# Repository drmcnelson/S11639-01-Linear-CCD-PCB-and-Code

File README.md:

# S11639-01-Linear-CCD-PCB-and-Code

By Dr M. C. Nelson, Copyright 2020-2025

Original repository [github.com/drmcnelson/S11639-01-Linear-CCD-PCB-and-Code](https://github.com/drmcnelson/S11639-01-Linear-CCD-PCB-and-Code)

This repo provides electronics, firmware and host software for the Hamamatsu S11639-01, a linear CCD sensor that has high sensitivity at 1300V/lx s and low dark noise at 0.2mV (for a 10msec exposure).  With saturation at 2V, the dynamic range is 10,000.
The electrical design is implemented as a two board set, sensor and controller, for mechanical stability and interchangeability.
The sensor board has the socketed sensor, logic gates to drive the pins, and a low noise all differential analog section with a high precision differential 16 bit ADC.
The controller operates the sensor and interacts with a host computer over USB, and has pins for trigger, gate, sync and busy signals.
The command interface is human readable ascii, data transfers are selectable in ascii or binary.

N.B.  This is an update to bring the S11639-0 board into compatibility with the new connector layout for our controller boards.   This design is not yet built, sponsors are welcome.  Please click the sponsor button at the top of the page.

*The original boards and their matching controllers are in the subdirecty labeled [Rev0Boards](./Rev0Boards).*

This version of the board is designed to be used with either of the our controllers, the [Teensy 4.0 based controller](https://github.com/drmcnelson/SPI-Instrumentation-Controller-T4.0) 
and the [Teensy 4.1 based controller](https://github.com/drmcnelson/SPI-Instrumentation-Controller-T4.1).
In principle, the S11639-01 could be used with a number of different Arduino boards.  After some extensive and detailed testing, we prefer the Teensy 4.x boards.  These have good implementations for 16 bit transfers over SPI and they have 480MHz USB for fast transfers to the host computer.

The firmware, which runs in the controller, provides high end functionality including clocked, triggered, and gated operation.
In the firmware, codes that are specific to the sensor are in a separate c++ file and header.  The "sketch file" implements a command interface and calls the sensor code to do the "work" of collecting frames in various operating modes.  The codes throughout, use the standard Arduino libraries plus a small number of optional register level enhancements for the i.MX RT MCU that provide faster and more constant interrupt latency and SPI transfers with less overhead.

## Sensor board details
The following image shows the circuit side of the sensor board with the high precision low noise differential front end (dual opamp lower right, adjacent to the video out pin from the sensor) interfaced to a differential 16bit 1MSPS ADC, and logic level converters (center) for the external digital interface.
The sensor is socketed on the reverse side. 
SPI and logic signals are brought to the double row header at the top edge of the board (ribbon cable compatible).
The external logic level is set by VDD supplied by the controller card.
Power for the sensor and other circuit elements is 5V and supplied by a separate connector.
The small jumper top center near the double row header, selects whether the CNVST pin on the ADC is connected to the TRG signal from the sensor or to the host processor.
(The firmware at present assumes the CNVST pin is connected to the MCU.)
The jumper and header (lower left) selects the internal 4.096V reference or provides a connector for an external reference.
The output from the analog section is available on the three pin header center bottom.
The trim pot should be set to 1.6V for sensors meeting the "typical" spec with output from 0.6V to 2.6V, there is a test point next to the trim pot labeled Voffset where the offset voltage can be measured.

## T4.0 Controller board details
Please refer to the repo at 
The following describes the T4.0 based controller. The double row header across the top matches that on the sensor board.  The two boards should be connected by a ribbon cable that can be a few inches in length, and by a two wire cable for power, between the connectors labeled "5V" upper left on this board and upper left on the sensor board.  (The power cable will cross over the ribbon cable when the boards are positioned correctly and joined by a ribbon cable.)
The single row headers provides access to the digital interface signals and provides additional pins to the right for a trigger input, sync and busy ouputs and spare digital I/O pin.   The double row header on the left provides access to the onboard analog digital converters and any of these can be used for digitial I/O.  While all of these have diode protection, users should be cognizant that the Teensy is not 5V tolerant. 

Running the supplied sketch (see the Firmware directory), the controller appears as a serial port or com port with a human readable command interface.  There is a help command that produces a listing of all of the available commands.  The device can collect (a) single frames, (b) clocked series of frames, (c) triggered single frames, (d) triggered sets of clocked frames (i.e. triggered kinetic series), and (e) gated frames.  There are commands to set the sense (hi/low) of the trigger input and each of the digital outputs, and to set whether the sync output is asserted at the beginning of each frame or series.  There is a "hold off" that can be used to triggered an external device and then wait for a fixed time before collecting a frame.  Busy is asserted whenever the device is active and until data has been transferred to the host computer.   A Python utility and class library and a C language utility and library provide two options for working with the device and integrating into equipment and experiments 

## T4.1 Controller board details
The Teensy 4.1 controller is similar to the T4.0 version, but with more connectors.
In the following image, the long connector across the top corresponds to the 20 connector in the T4.0 controller.  This where the CCD connects. 
Filtered +5V power comes from the connector on the lower right.
The keyed connectors on the left, top and bottom are SPI interfaces 0 and 1.
Analog inputs are to the right of the SPI1 connector
Trigger, sync and busy are implemented in firmware on pins 0, 1, and 2.  These are brought out to a the double row header upper right, so that each pin has a ground pin.
The single row headers provide monitoring points and extended set of digital I/O pins.

## Example Spectrometer
The following shows a spectrometer built with the S11639-0 and a fluorescent lamp spectrum collected through an optical fiber and 200um slit and single 100ms exposure, with the fluorescent ceiling lamp at a distance of about 2 meters from the end of the fiber.  (At a 10ms exposure the background is 0.5mV as listed in the datasheet for the sensor.) The sensor board is mounted in a frame that allows adjustment to position the sensor on the focus.  The control board is mounted outside on the light tight cover, for easy access to the pins without disturibing the sensor board, and connected to the sensor board via a 5 inch long ribbon cable and power (twisted red and black wires). Notice that all of the optical mounts are 3-d printed.  The base plate was purchased on Amazon, the sma905 port, slit and lenses on ebay and the transmission grating from Thorlabs.

## Availability and Sponsorhip
This repo and its contents are provided without warranty or representation of suitability for any purpose whatsoever.

Feel free to build this for your own use or in your lab.  The intent is to support access to doing good science for those who are not as well funded as others.  Commercial use is subject to review and approval, per this criterion.

If you would like a preassembled board, please consider sponsoring and please contact me so that I can get a current cost of materials.

Sponsorship is very much appreciated.  Please click the sponsor button and help us make this and more devices available and support our effort to make doing science more accessible.

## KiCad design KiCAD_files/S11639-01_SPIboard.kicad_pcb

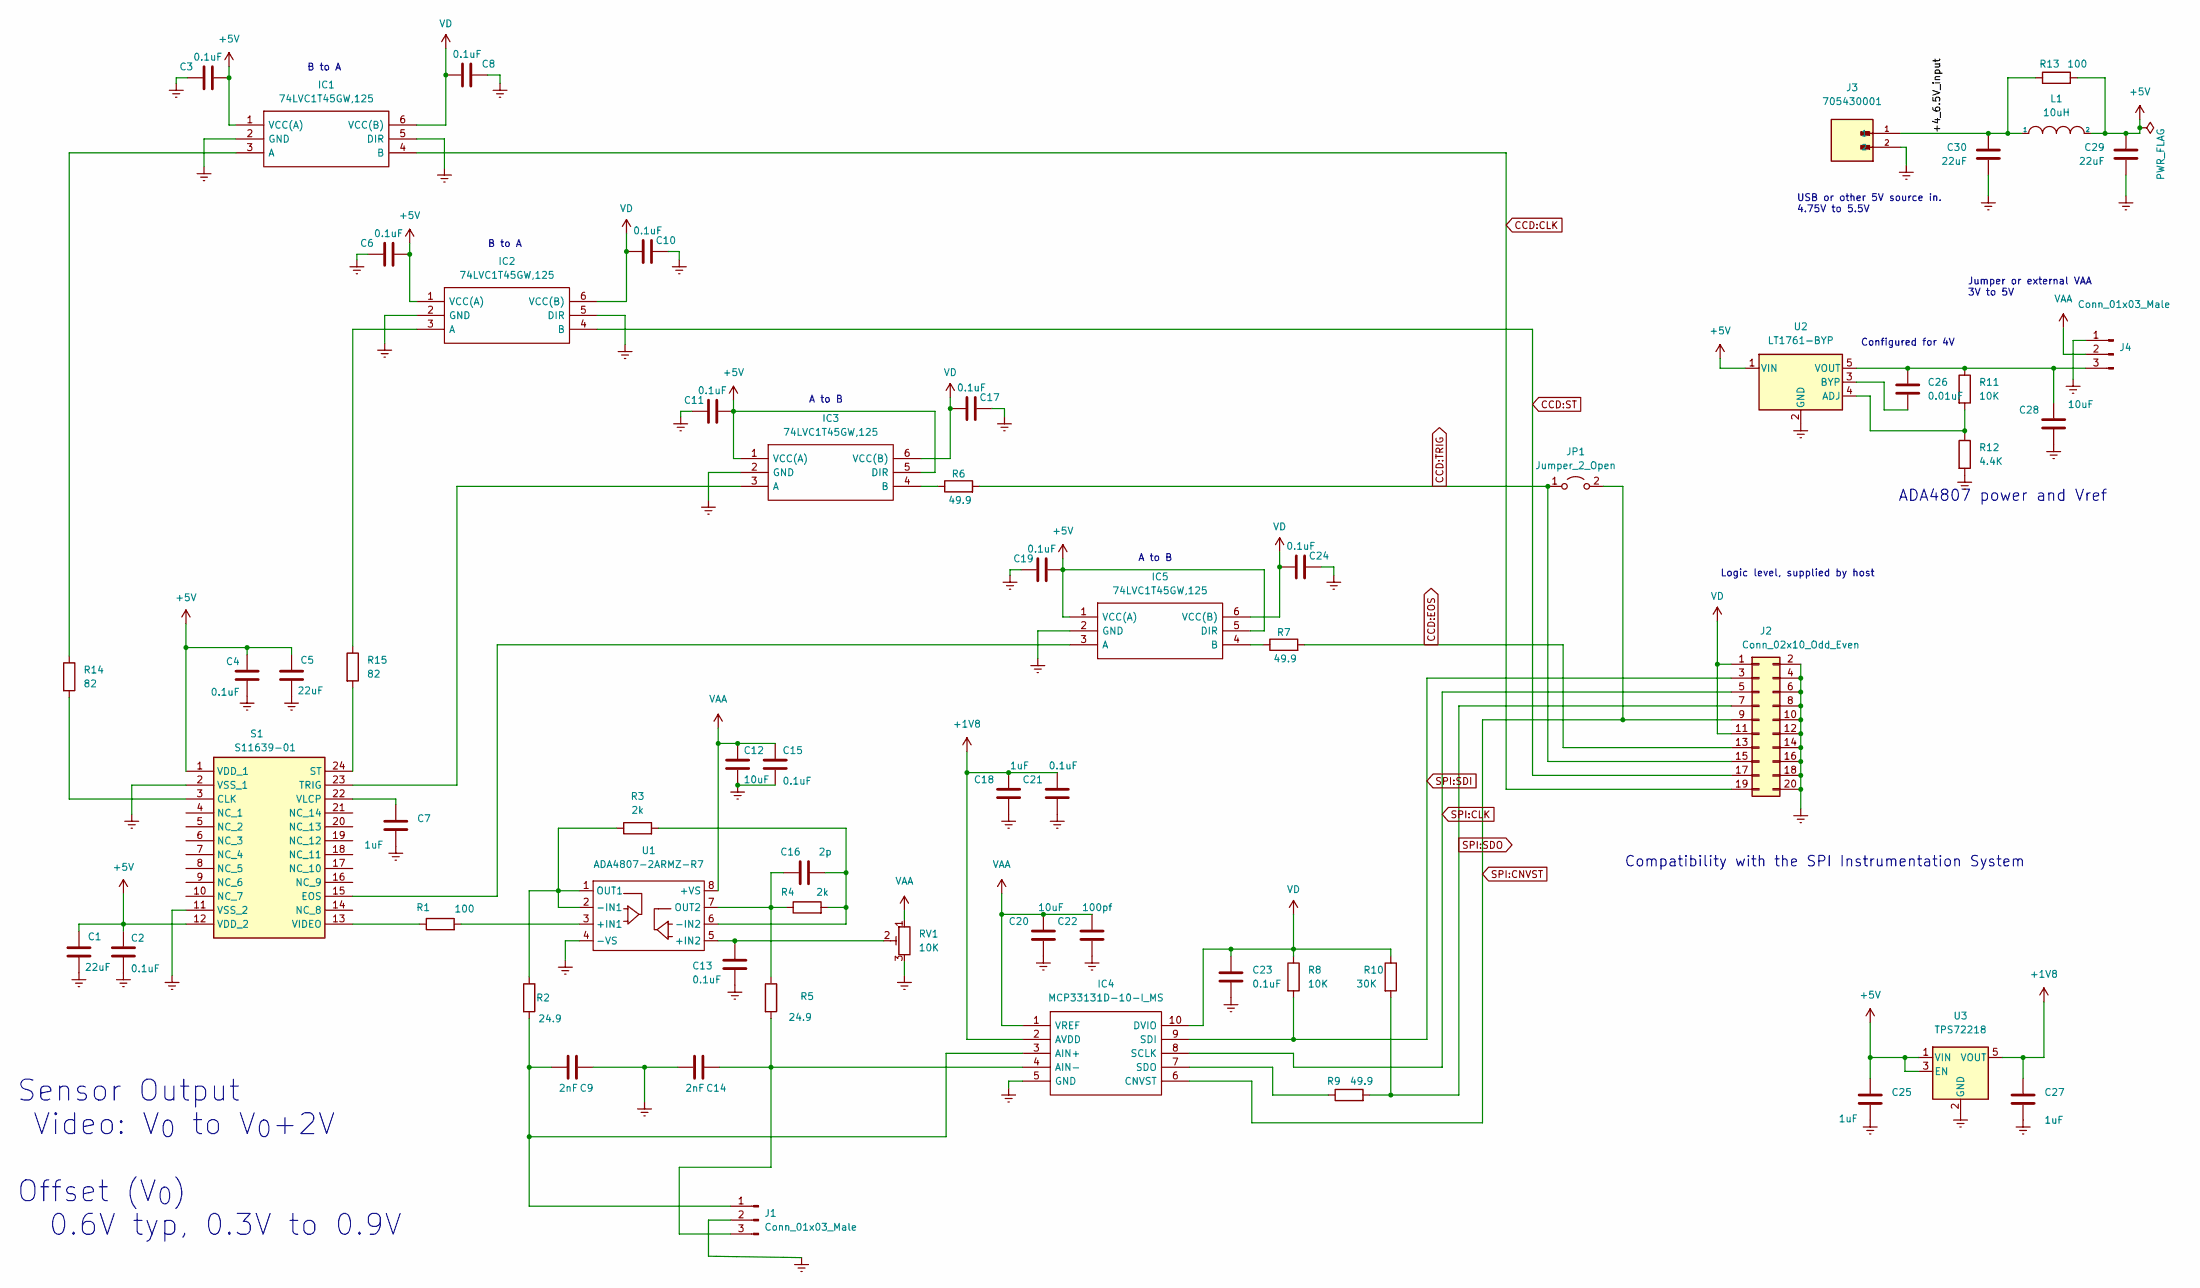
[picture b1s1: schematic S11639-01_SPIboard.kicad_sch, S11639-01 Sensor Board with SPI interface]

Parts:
C1, C5, C29, C30: 22uF; C_0805_2012Metric; Digikey 311-1903-1-ND
C2, C3, C4, C6, C8, C10, C11, C13, C15, C17, C19, C21, C23, C24: 0.1uF; C_0603_1608Metric; Digikey 445-5666-1-ND
C7, C18, C25, C27: 1uF; C_0603_1608Metric; Digikey 490-10673-1-ND
C9, C14: 2nF; C_0603_1608Metric; Digikey 311-1743-1-ND
C12, C20, C28: 10uF; C_0603_1608Metric; Digikey 490-18214-1-ND
C16: 2p; C_0603_1608Metric; Digikey 311-3827-1-ND
C22: 100pf; C_0603_1608Metric; Digikey 399-17391-1-ND
C26: 0.01uF; C_0402_1005Metric; Digikey 311-1337-1-ND
IC1, IC2, IC3, IC5: 74LVC1T45GW,125; SOT65P210X110-6N; Manufacturer_Part_Number 74LVC1T45GW,125; Digikey 1727-4560-1-ND
IC4: MCP33131D-10-I_MS; MSOP-10_3x3mm_P0.5mm; Manufacturer_Part_Number MCP33131D-10-I/MS; Mouser Part Number 579-MCP33131D10IMS
J1, J4: Conn_01x03_Male; PinHeader_1x03_P2.54mm_Vertical; Digikey 3M156268-03-ND
J2: Conn_02x10_Odd_Even; PinHeader_2x10_P2.54mm_Vertical; Digikey 3M156308-20-ND
J3: 705430001; MOLEX_705430001; PARTREV M1; Digikey WM4800-ND
JP1: Jumper_2_Open; PinHeader_1x02_P1.27mm_Vertical; Digikey S9014E-02-ND
L1: 10uH; L_Taiyo-Yuden_NR-40xx; Digikey 587-2886-1-ND
R1, R13: 100; R_0603_1608Metric; Digikey RNCP0603FTD100RCT-ND
R2, R5: 24.9; R_0603_1608Metric; Digikey 2019-RK73H1JTTD24R9FCT-ND
R3, R4: 2k; R_0603_1608Metric; Digikey P2.0KDBCT-ND
R6, R7, R9: 49.9; R_0603_1608Metric; Digikey RMCF0603FT49R9CT-ND
R8: 10K; R_0603_1608Metric; Digikey 311-10.0KHRCT-ND
R10: 30K; R_0603_1608Metric; Digikey 311-30.0KHRCT-ND
R11: 10K; R_0402_1005Metric; Digikey A127415CT-ND
R12: 4.4K; R_0402_1005Metric; Digikey YAG4274CT-ND
R14, R15: 82; R_0603_1608Metric; Digikey 311-82.0HRCT-ND
RV1: 10K; TRIM_3296W-1-502LF; Digikey 3296W-103LF-ND
S1: S11639-01; DIP-24_W10.16mm_Socket; Manufacturer_Part_Number S11639-01
U1: ADA4807-2ARMZ-R7; MSOP-8_3x3mm_P0.65mm; Digikey ADA4807-2ARMZ-R7CT-ND
U2: LT1761-BYP; TSOT-23-5; Digikey 505-LT1761ES5-BYP#TRMPBFCT-ND
U3: TPS72218; SOT-23-5; Digikey 296-12523-1-ND

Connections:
+1V8: C18.1, C21.1, C27.1, IC4.2 (AVDD), U3.5 (VOUT)
+5V: C1.1, C2.1, C3.1, C4.1, C5.1, C6.1, C11.1, C19.1, C25.1, C29.1, IC1.1 (VCC(A)), IC2.1 (VCC(A)), IC3.1 (VCC(A)), IC3.5 (DIR), IC5.1 (VCC(A)), IC5.5 (DIR), L1.2, R13.2, S1.1 (VDD_1), S1.12 (VDD_2), U2.1 (VIN), U3.1 (VIN), U3.3 (EN)
/+4_6.5V_input: C30.1, J3.1, L1.1, R13.1
CCD:CLK: IC1.4 (B), J2.19
CCD:EOS: J2.13, R7.2
CCD:ST: IC2.4 (B), J2.17
CCD:TRIG: J2.15, JP1.1 (A), R6.2
Earth: C1.2, C2.2, C3.2, C4.2, C5.2, C6.2, C7.2, C8.2, C9.1, C10.2, C11.2, C12.2, C13.2, C14.2, C15.2, C17.2, C18.2, C19.2, C20.2, C21.2, C22.2, C23.2, C24.2, C25.2, C27.2, C28.2, C29.2, C30.2, IC1.2 (GND), IC1.5 (DIR), IC2.2 (GND), IC2.5 (DIR), IC3.2 (GND), IC4.5 (GND), IC5.2 (GND), J1.2, J2.2, J2.4, J2.6, J2.8, J2.10, J2.12, J2.14, J2.16, J2.18, J2.20, J3.2, J4.1, R12.2, RV1.3, S1.2 (VSS_1), S1.11 (VSS_2), U1.4 (-VS), U2.2 (GND), U3.2 (GND)
unnamed: IC1.3 (A), R14.1
unnamed: IC2.3 (A), R15.1
unnamed: IC3.3 (A), S1.23 (TRIG)
unnamed: IC3.4 (B), R6.1
unnamed: C9.2, IC4.3 (AIN+), J1.1, R2.2
unnamed: C14.1, IC4.4 (AIN-), J1.3, R5.2
unnamed: IC4.7 (SDO), R9.1
unnamed: IC5.3 (A), S1.15 (EOS)
unnamed: IC5.4 (B), R7.1
unnamed: C26.1, C28.1, J4.3, R11.1, U2.5 (VOUT)
unnamed: R14.2, S1.3 (CLK)
unnamed: R15.2, S1.24 (ST)
unnamed: R1.1, S1.13 (VIDEO)
unnamed: C7.1, S1.22 (VLCP)
unnamed: R1.2, U1.3 (+IN1)
unnamed: C13.1, RV1.2, U1.5 (+IN2)
unnamed: R2.1, R3.1, U1.1 (OUT1), U1.2 (-IN1)
unnamed: C16.2, R3.2, R4.2, U1.6 (-IN2)
unnamed: C16.1, R4.1, R5.1, U1.7 (OUT2)
unnamed: R11.2, R12.1, U2.4 (ADJ)
unnamed: C26.2, U2.3 (BYP)
SPI:CLK: IC4.8 (SCLK), J2.5
SPI:CNVST: IC4.6 (CNVST), J2.9, JP1.2 (B)
SPI:SDI: IC4.9 (SDI), J2.3, R8.2
SPI:SDO: J2.7, R9.2, R10.2
VAA: C12.1, C15.1, C20.1, C22.1, IC4.1 (VREF), J4.2, RV1.1, U1.8 (+VS)
VD: C8.1, C10.1, C17.1, C23.1, C24.1, IC1.6 (VCC(B)), IC2.6 (VCC(B)), IC3.6 (VCC(B)), IC4.10 (DVIO), IC5.6 (VCC(B)), J2.1, J2.11, R8.1, R10.1

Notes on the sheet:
B to A
USB or other 5V source in. 4.75V to 5.5V
A to B
Compatibility with the SPI Instrumentation System
Logic level, supplied by host
Jumper or external VAA 3V to 5V
Configured for 4V
ADA4807 power and Vref
Sensor Output Video: V_{0} to V_{0}+2V Offset (V_{0}) 0.6V typ, 0.3V to 0.9V

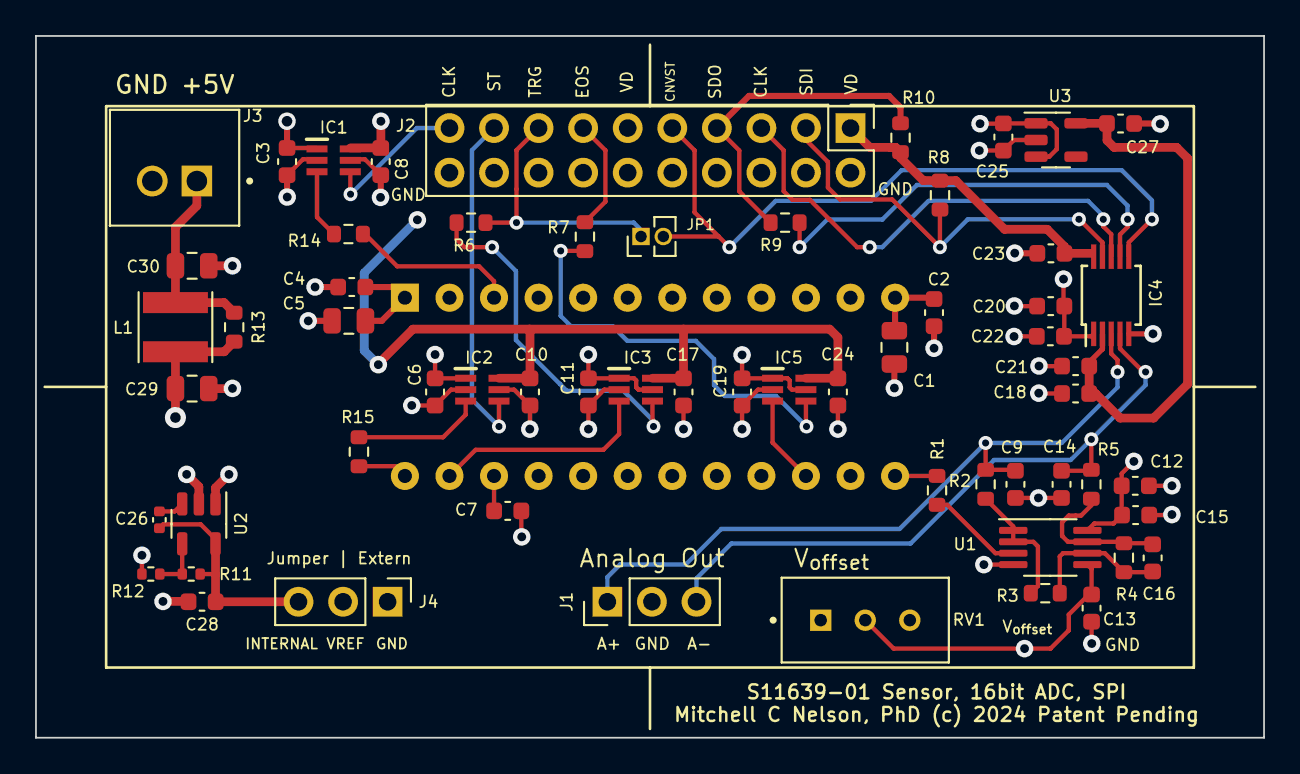
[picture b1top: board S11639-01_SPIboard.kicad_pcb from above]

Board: 4 copper layers, 70.0 x 40.0 mm, 61 parts (1 on the bottom side), 35 nets.

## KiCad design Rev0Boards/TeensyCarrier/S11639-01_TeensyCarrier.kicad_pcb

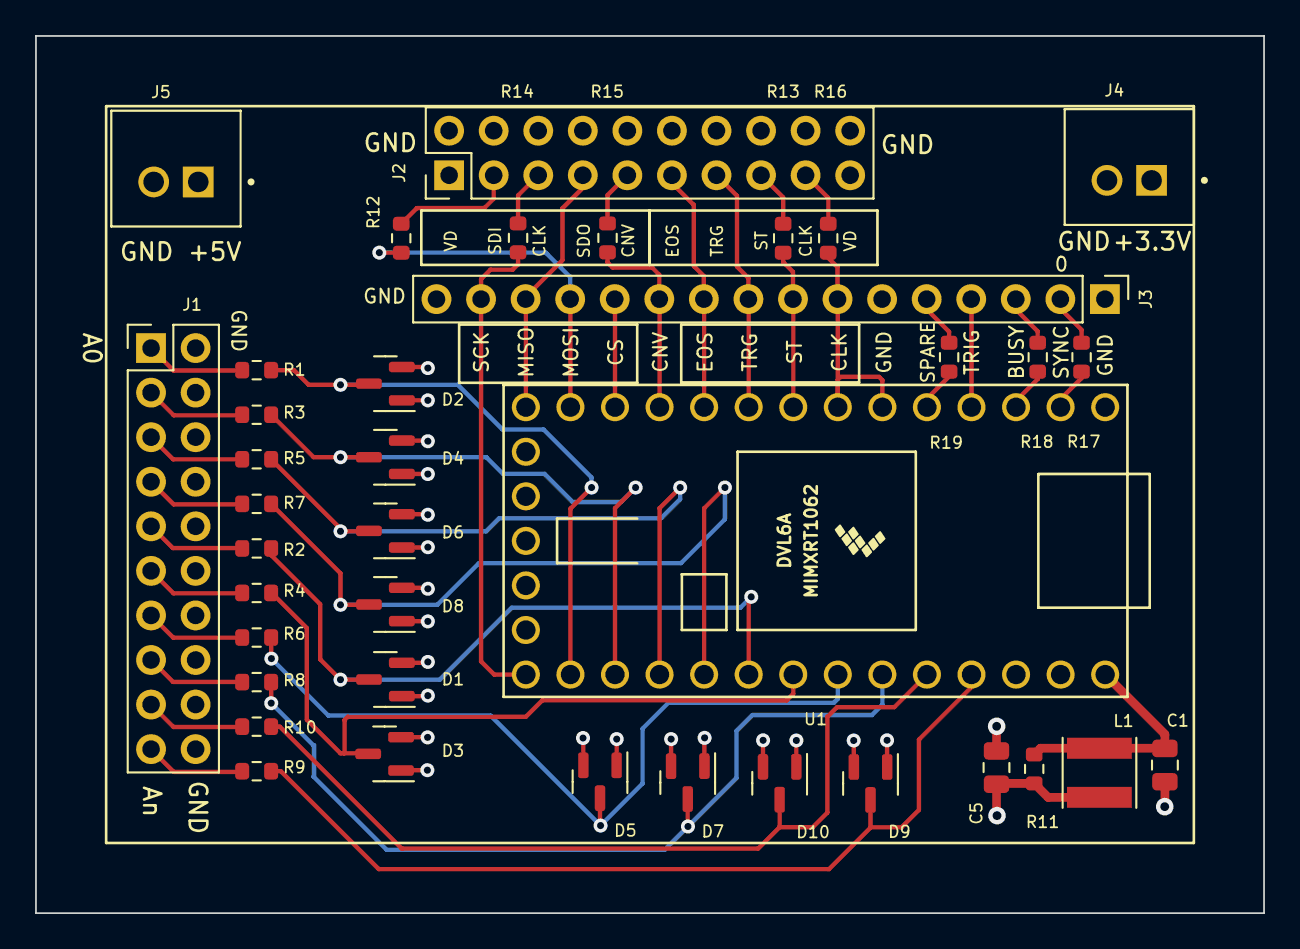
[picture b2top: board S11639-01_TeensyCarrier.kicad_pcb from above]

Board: 4 copper layers, 70.0 x 50.0 mm, 38 parts (0 on the bottom side), 45 nets.

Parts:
C1, C5: 22uF; C_0805_2012Metric
D1, D2, D3, D4, D5, D6, D7, D8, D9, D10: BAV99; SOT-23
J1, J2: Conn_02x10_Odd_Even; PinHeader_2x10_P2.54mm_Vertical
J3: Conn_01x16_Male; PinHeader_1x16_P2.54mm_Vertical
J4, J5: 705430001; MOLEX_705430001
L1: 10uH; L_Taiyo-Yuden_NR-40xx
R1, R2, R3, R4, R5, R6, R7, R8, R9, R10, R11: 100R; R_0603_1608Metric
R12, R13, R14, R15, R16, R17, R18, R19: 49.9; R_0603_1608Metric
U1: Teensy4.0; Teensy40

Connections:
+3.3V: D1.2 (A), D2.2 (A), D3.2 (A), D4.2 (A), D5.2 (A), D6.2 (A), D7.2 (A), D8.2 (A), D9.2 (A), D10.2 (A), J2.1, J2.19, J4.1, U1.31 (3V3)
+5V: C5.1, J5.1, L1.2, R11.2
CCD:CLK: J2.17, R16.1
CCD:EOS: J2.11, J3.10, U1.10 (8_TX2_IN1)
CCD:ST: J2.15, R13.1
CCD:TRIG: J2.13, J3.9, U1.9 (7_RX2_OUT1A)
Earth: C1.2, C5.2, D1.1 (K), D2.1 (K), D3.1 (K), D4.1 (K), D5.1 (K), D6.1 (K), D7.1 (K), D8.1 (K), D9.1 (K), D10.1 (K), J1.2, J1.4, J1.6, J1.8, J1.10, J1.12, J1.14, J1.16, J1.18, J1.20, J2.2, J2.4, J2.6, J2.8, J2.10, J2.12, J2.14, J2.16, J2.18, J2.20, J3.1, J3.6, J3.16, J4.2, J5.2, U1.1 (GND), U1.32 (GND)
unnamed: C1.1, L1.1, R11.1, U1.33 (VIN)
unnamed: D1.3 (K), R2.2, U1.25 (18_A4_SDA0)
unnamed: D2.3 (K), R1.2, U1.21 (14_A0_TX3_SPDIF_OUT)
unnamed: D3.3 (K), R4.2, U1.26 (19_A5_SCL0)
unnamed: D4.3 (K), R3.2, U1.22 (15_A1_RX3_SPDIF_IN)
unnamed: D5.3 (K), R6.2, U1.27 (20_A6_TX5_LRCLK1)
unnamed: D6.3 (K), R5.2, U1.23 (16_A2_RX4_SCL1)
unnamed: D7.3 (K), R8.2, U1.28 (21_A7_RX5_BCLK1)
unnamed: D8.3 (K), R7.2, U1.24 (17_A3_TX4_SDA1)
unnamed: D9.3 (K), R9.2, U1.30 (23_A9_CRX1_MCLK1)
unnamed: D10.3 (K), R10.2, U1.29 (22_A8_CTX1)
unnamed: J1.1, R1.1
unnamed: J1.3, R3.1
unnamed: J1.5, R5.1
unnamed: J1.7, R7.1
unnamed: J1.9, R2.1
unnamed: J1.11, R4.1
unnamed: J1.13, R6.1
unnamed: J1.15, R8.1
unnamed: J1.17, R10.1
unnamed: J1.19, R9.1
unnamed: J2.3, R12.1
unnamed: J3.2, R17.1
unnamed: J3.3, R18.1
unnamed: J3.4, U1.4 (2_OUT2)
unnamed: J3.5, R19.1
unnamed: J3.7, R16.2, U1.6 (4_BCLK2), U1.7 (5_IN2)
unnamed: J3.8, R13.2, U1.8 (6_OUT1D)
unnamed: J3.11, R15.2, U1.11 (9_OUT1C)
unnamed: J3.12, U1.12 (10_CS_MQSR)
unnamed: J3.13, R12.2, U1.13 (11_MOSI_CTX1)
unnamed: J3.15, R14.2, U1.20 (13_SCK_CRX1_LED)
unnamed: R17.2, U1.2 (0_RX1_CRX2_CS1)
unnamed: R18.2, U1.3 (1_TX1_CTX2_MISO1)
unnamed: R19.2, U1.5 (3_LRCLK2)
SPI:CLK: J2.5, R14.1
SPI:CNVST: J2.9, R15.1
SPI:SDO: J2.7, J3.14, U1.14 (12_MISO_MQSL)

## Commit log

2024-03-21 Version 0.2, tested
    Tested, noise is 0.5mV in , per spec for the part. See the firmware directory for an Arduino sketch to use the board. See the Teensy Carrier for a mating board that hosts a Teensy 4.0 to run the sens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
2024-03-21 Full feature code to run the sensor board
2024-03-21 Update README.md
    Updating the readme and files
2024-03-22 Update ADC timing and add erase command for stored parameters
2024-03-25 Add faster SPI option
2024-12-26 Update permissions and sponshorship
2024-12-26 Add detail, two controller options and sponsorship
2024-12-26 Add details, two controller options and sponsorship
2025-03-25 upgrade input power filter
    Adds input side cap to the inductive input filter.

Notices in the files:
KiCAD/S11639-01_SPIboard.kicad_sch:
Mitchell C Nelson, PhD  (C) 2023
KiCAD_files/S11639-01_SPIboard.kicad_pcb:
Mitchell C Nelson, PhD (c) 2024 Patent Pending
KiCAD_files/S11639-01_SPIboard.kicad_sch:
Mitchell C Nelson, PhD  (C) 2023, 2024
